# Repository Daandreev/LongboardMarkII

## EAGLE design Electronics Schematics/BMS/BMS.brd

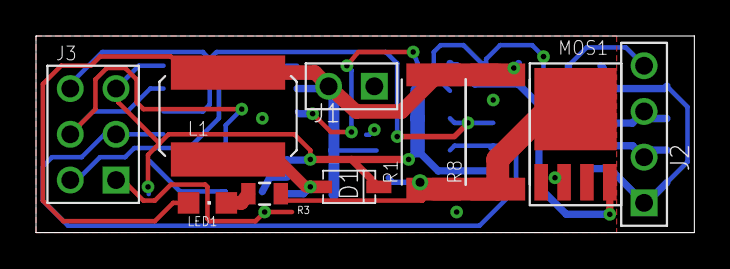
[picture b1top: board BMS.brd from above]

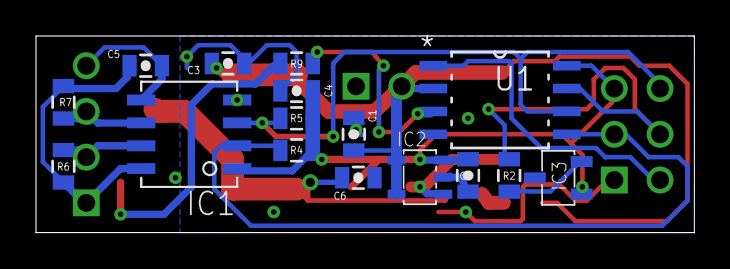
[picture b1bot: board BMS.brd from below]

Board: 2 copper layers, 36.6 x 10.9 mm, 26 parts (16 on the bottom side), 17 nets.

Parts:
C1, C2, C3, C4, C5, C6: 10uF; 0805-CAP
D1: DIODE_SCHOTTKYSOD-123; SOD-123
IC1: SI8600_DUALCHANNELISO; SOIC-8
IC2: SP6641; SOT-23
IC3: TEMP_MCP9701; SOT-23-3
J1: CONNECTOR_2PIN; 2PIN_.1'
J2: CONNECTOR_4PIN; 4PIN_.1'
J3: ISPHEADER; 2X3PIN_.1'
L1: 22uH; 6X6MM_IND
LED1: CHIPLED_0805
MOS1: MOS_N_LOGIC_PSMN7R0; LFPAK
R1, R8: 3.3; 2512_(6432_METRIC)
R2, R3: 390; 0805
R4, R5, R6, R7: 10k; 0805
R9: 180; 0805
U1: ATTINY85-20SU; SOIC127P798X216-8N

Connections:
5V: C2.1, C4.1, D1.CATHODE, IC1.P$1, IC2.3, IC3.1, J3.P$2, R4.2, R5.2, U1.8
5V_VIR: C5.1, IC1.P$8, J2.P$1, R6.2, R7.2
GATE: R9.1, U1.3
GND: C1.1, C2.2, C3.2, C4.2, C6.2, IC1.P$4, IC2.2, IC3.3, J1.P$1, J3.P$6, MOS1.P$1, MOS1.P$2, MOS1.P$3, U1.4
GND_VIR: C5.2, IC1.P$5, J2.P$4
MISO: IC1.P$3, J3.P$1, R5.1, U1.6
MOSI: IC1.P$2, J3.P$4, R4.1, U1.5
unnamed: MOS1.P$4, R9.2
unnamed: LED1.C, R3.2
unnamed: C6.1, MOS1.P$5, R1.P$1, R3.1, R8.P$1
unnamed: IC3.2, R2.2
unnamed: D1.ANODE, IC2.1, L1.P$1
RESET: J3.P$5, U1.1
SCK: J3.P$3, R2.1, U1.7
SCL: IC1.P$6, J2.P$3, R7.1
SDA: IC1.P$7, J2.P$2, R6.1
VBAT: C1.2, C3.1, IC2.4, IC2.5, J1.P$2, L1.P$2, LED1.A, R1.P$2, R8.P$2, U1.2

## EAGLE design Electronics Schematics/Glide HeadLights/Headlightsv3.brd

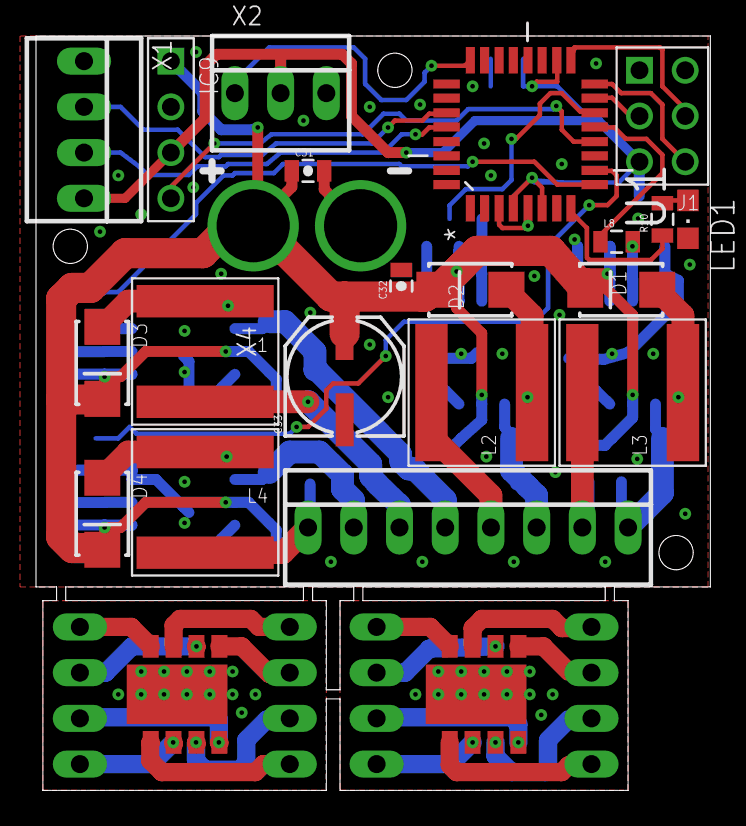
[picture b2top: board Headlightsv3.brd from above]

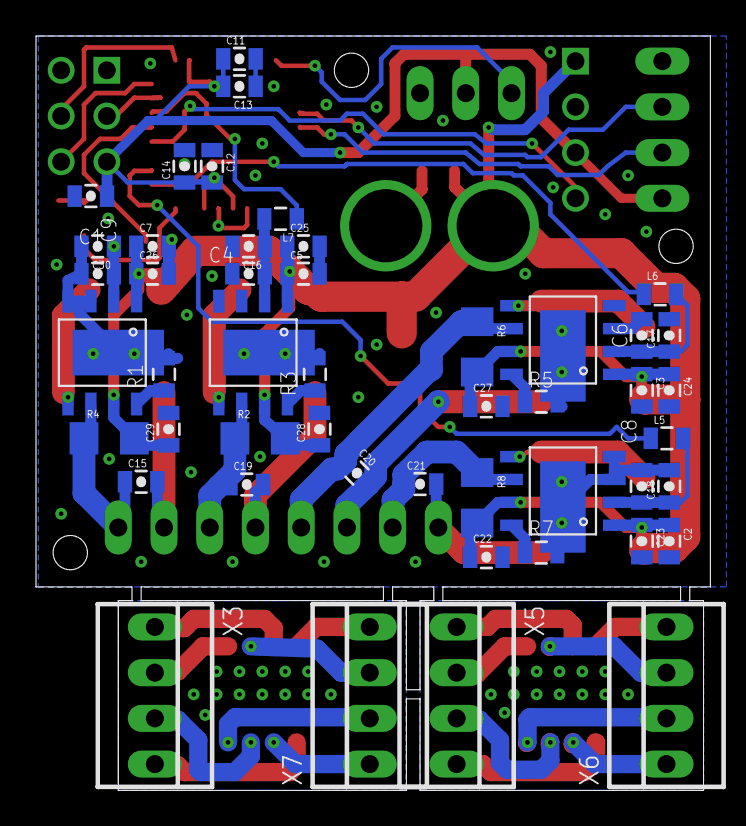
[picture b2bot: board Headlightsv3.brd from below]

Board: 2 copper layers, 37.5 x 41.9 mm, 70 parts (48 on the bottom side), 52 nets.

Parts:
C1, C4, C6, C8: 10uF; 0805-CAP
C2, C3, C5, C7, C9, C13, C14, C15, C19, C20, C21, C22, C27, C28, C29, C32: 1uF; 0805-CAP
C11, C12, C16, C17, C18, C23, C24, C25, C26, C30, C31: 0.1uF; 0805-CAP
C33: NIPPON_F80
D1, D2, D3, D4: SMA-DIODE_ALT
IC1, IC3, IC4, IC5: ILD6150_LED_DRIVER; PG-DSO-8-27
IC2, IC6: LED_RGBW_CONF2; LED_RGBW_CUSTOM
IC9: 5VBUCK_DANNY_CUSTOM_PCB; 4PIN_.1'
J1: ISPHEADER; 2X3PIN_.1'
L1, L2, L3, L4: 33uH; 8X8MM_IND
L5, L6, L7, L8: 0805
LED1: CHIPLED_0805
R1, R3, R5, R7: 10k; 0805
R2, R4, R6, R8: .22; 1206
R10: 1k; 0805
U1: ATMEGA328P-AU; QFP80P900X900X120-32N
X1, X3, X5, X6, X7: 22-23-2041
X2: 22-23-2031
X4: 22-23-2081

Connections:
5V: C9.1, C11.1, C12.2, C13.2, C14.1, IC9.P$3, J1.P$2, U1.4, U1.6, U1.18, X1.4, X2.2
BA: C20.2, L1.P$1, X4.3
BA1: IC6.6, X7.3
BAO: IC2.6, X6.3
BC: C20.1, IC4.P$6, R6.1, X4.4
BC1: IC6.5, X3.2
BCO: IC2.5, X5.2
DIMB: L6.1, U1.9
DIMG: L7.1, U1.14
DIMR: L8.1, U1.13
DIMW: L5.1, U1.10
GA: C19.2, L2.P$1, X4.5
GA1: IC6.4, X7.2
GAO: IC2.4, X6.2
GC: C19.1, IC3.P$6, R2.1, X4.6
GC1: IC6.3, X3.3
GCO: IC2.3, X5.3
GND: C1.2, C2.2, C3.2, C4.2, C5.2, C6.2, C7.2, C8.2, C9.2, C11.2, C12.1, C13.1, C14.2, C16.2, C17.2, C18.2, C22.2, C23.2, C24.2, C25.2, C26.2, C27.2, C28.2, C29.2, C30.2, C31.2, C32.2, C33.-, IC1.P$3, IC1.P$4, IC1.P$9, IC3.P$3, IC3.P$4, IC3.P$9, IC4.P$3, IC4.P$4, IC4.P$9, IC5.P$3, IC5.P$4, IC5.P$9, IC9.P$2, J1.P$6, LED1.C, R1.2, R3.2, R5.2, R7.2, U1.3, U1.5, X1.1, X2.3
LEDG: R10.1, U1.8
MISO: J1.P$1, U1.16
MOSI: J1.P$4, U1.15
unnamed: IC1.P$8, R1.1
unnamed: IC3.P$8, R3.1
unnamed: D2.A, IC3.P$5, L2.P$2
unnamed: IC4.P$8, R5.1
unnamed: D1.A, IC1.P$5, L3.P$2
unnamed: D3.A, IC4.P$5, L1.P$2
unnamed: IC5.P$8, R7.1
unnamed: D4.A, IC5.P$5, L4.P$2
unnamed: LED1.A, R10.2
PWMB: C6.1, C17.1, IC4.P$2, L6.2
PWMG: C4.1, C16.1, IC3.P$2, L7.2
PWMR: C1.1, C30.1, IC1.P$2, L8.2
PWMW: C8.1, C18.1, IC5.P$2, L5.2
RA: C15.2, L3.P$1, X4.7
RA1: IC6.2, X7.1
RAO: IC2.2, X6.1
RC: C15.1, IC1.P$6, R4.1, X4.8
RC1: IC6.1, X3.4
RCO: IC2.1, X5.4
SCK: J1.P$3, U1.17
SCL: U1.28, X1.3
SDA: U1.27, X1.2
SHDN: IC9.P$4, U1.12
TEMP1: U1.24, X2.1
VBAT: C2.1, C3.1, C5.1, C7.1, C22.1, C23.1, C24.1, C25.1, C26.1, C27.1, C28.1, C29.1, C31.1, C32.1, C33.+, D1.C, D2.C, D3.C, D4.C, IC1.P$1, IC1.P$7, IC3.P$1, IC3.P$7, IC4.P$1, IC4.P$7, IC5.P$1, IC5.P$7, IC9.P$1, R2.2, R4.2, R6.2, R8.2
WA: C21.2, L4.P$1, X4.1
WA1: IC6.8, X7.4
WAO: IC2.8, X6.4
WC: C21.1, IC5.P$6, R8.1, X4.2
WC1: IC6.7, X3.1
WCO: IC2.7, X5.1

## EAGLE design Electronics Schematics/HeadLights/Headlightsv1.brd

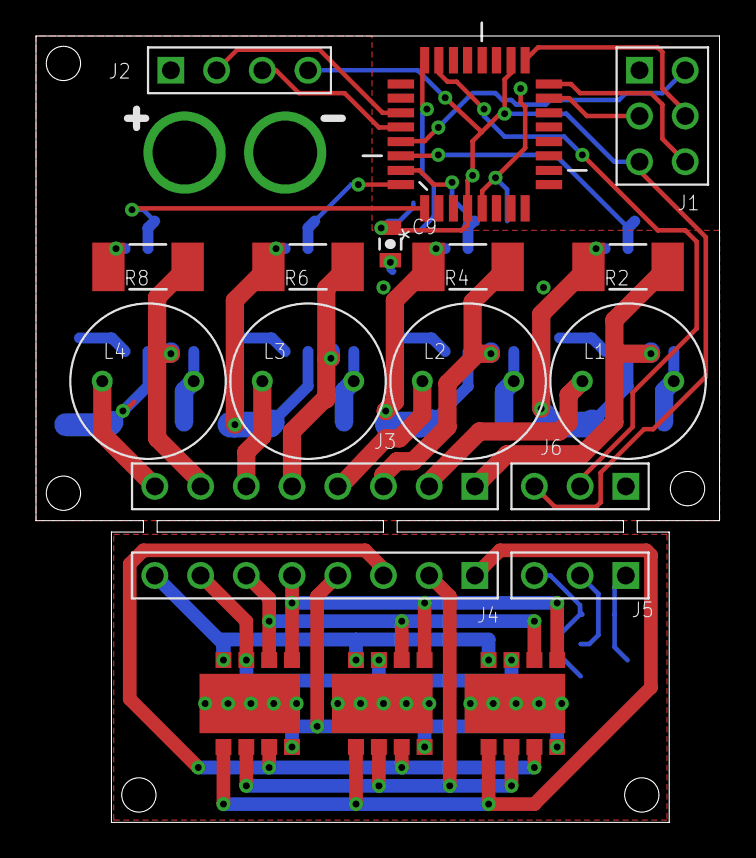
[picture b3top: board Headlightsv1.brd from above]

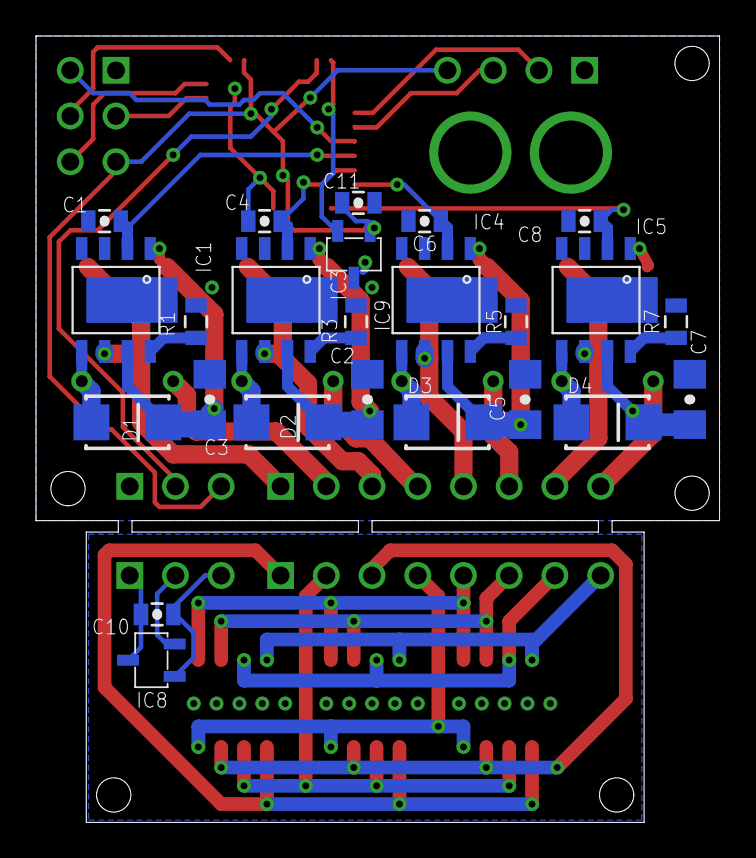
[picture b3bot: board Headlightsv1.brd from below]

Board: 2 copper layers, 38.0 x 43.7 mm, 43 parts (24 on the bottom side), 43 nets.

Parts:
C1, C4, C6, C8: 10uF; 0805-CAP
C2, C3, C5, C7: 1uF; 1206-CAP
C9, C10, C11: 0.33uF; 0805-CAP
D1, D2, D3, D4: SMA-DIODE_ALT
IC1, IC3, IC4, IC5: ILD6150_LED_DRIVER; PG-DSO-8-27
IC2, IC6, IC7: LED_RGBW_CONF2; LED_RGBW_CUSTOM
IC8, IC9: TEMP_MCP9701; SOT-23-3
J1: ISPHEADER; 2X3PIN_.1'
J2: CONNECTOR_4PIN; 4PIN_.1'
J3, J4: CONNECTOR_8PIN; 8PIN_.1'
J5, J6: CONNECTOR_3PIN; 3PIN_.1'
L1, L2, L3, L4: 33uH; IND_RLB_SERIES
R1, R3, R5, R7: 10k; 0805
R2, R4, R6, R8: .11; R2010
U1: ATTINY48-AU; QFP80P900X900X120-32N

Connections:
5V: C9.1, C11.1, IC9.1, J1.P$2, J2.P$4, J6.P$3, U1.4, U1.18
5VO: C10.2, IC8.1, J5.P$3
BA: J3.P$6, L3.P$1
BAO: IC2.6, IC6.6, IC7.6, J4.P$6
BC: IC4.P$6, J3.P$5, R6.1
BCO: IC2.5, IC6.5, IC7.5, J4.P$5
DIMB: C6.1, IC4.P$2, U1.32
DIMG: C4.1, IC3.P$2, U1.31
DIMR: C1.1, IC1.P$2, U1.30
DIMW: C8.1, IC5.P$2, U1.1
GA: J3.P$4, L2.P$1
GAO: IC2.4, IC6.4, IC7.4, J4.P$4
GC: IC3.P$6, J3.P$3, R4.1
GCO: IC2.3, IC6.3, IC7.3, J4.P$3
GND: C1.2, C2.2, C3.2, C4.2, C5.2, C6.2, C7.2, C8.2, C9.2, C11.2, IC1.P$3, IC1.P$4, IC1.P$9, IC3.P$3, IC3.P$4, IC3.P$9, IC4.P$3, IC4.P$4, IC4.P$9, IC5.P$3, IC5.P$4, IC5.P$9, IC9.3, J1.P$6, J2.P$1, J6.P$1, R1.2, R3.2, R5.2, R7.2, U1.5
GNDO: C10.1, IC8.3, J5.P$1
HEAT: IC2.9, IC6.9, IC7.9
MISO: J1.P$1, U1.16
MOSI: J1.P$4, U1.15
unnamed: IC1.P$8, R1.1
unnamed: IC3.P$8, R3.1
unnamed: D2.A, IC3.P$5, L2.P$2
unnamed: IC4.P$8, R5.1
unnamed: D1.A, IC1.P$5, L1.P$2
unnamed: D3.A, IC4.P$5, L3.P$2
unnamed: IC5.P$8, R7.1
unnamed: D4.A, IC5.P$5, L4.P$2
RA: J3.P$2, L1.P$1
RAO: IC2.2, IC6.2, IC7.2, J4.P$2
RC: IC1.P$6, J3.P$1, R2.1
RCO: IC2.1, IC6.1, IC7.1, J4.P$1
RESET: J1.P$5, U1.29
SCK: J1.P$3, U1.17
SCL: J2.P$3, U1.28
SDA: J2.P$2, U1.27
TEMP1: J6.P$2, U1.23
TEMP1O: IC8.2, J5.P$2
TEMP2: IC9.2, U1.24
VBAT: C2.1, C3.1, C5.1, C7.1, D1.C, D2.C, D3.C, D4.C, IC1.P$1, IC1.P$7, IC3.P$1, IC3.P$7, IC4.P$1, IC4.P$7, IC5.P$1, IC5.P$7, R2.2, R4.2, R6.2, R8.2
WA: J3.P$8, L4.P$1
WAO: IC2.8, IC6.8, IC7.8, J4.P$8
WC: IC5.P$6, J3.P$7, R8.1
WCO: IC2.7, IC6.7, IC7.7, J4.P$7

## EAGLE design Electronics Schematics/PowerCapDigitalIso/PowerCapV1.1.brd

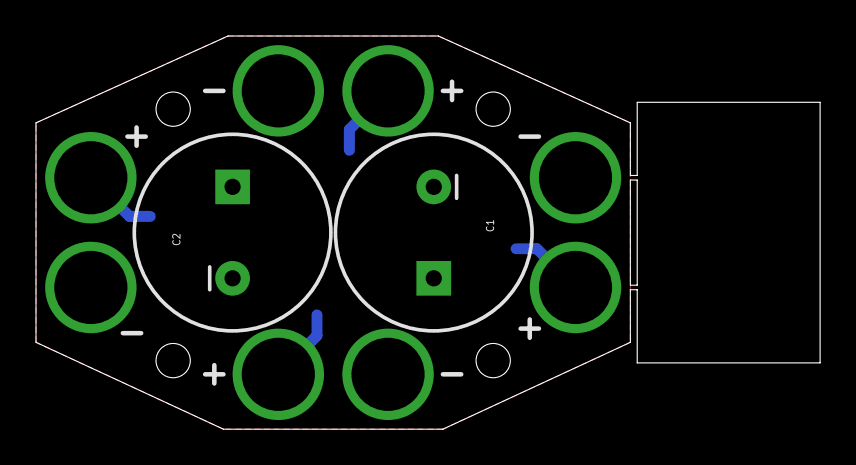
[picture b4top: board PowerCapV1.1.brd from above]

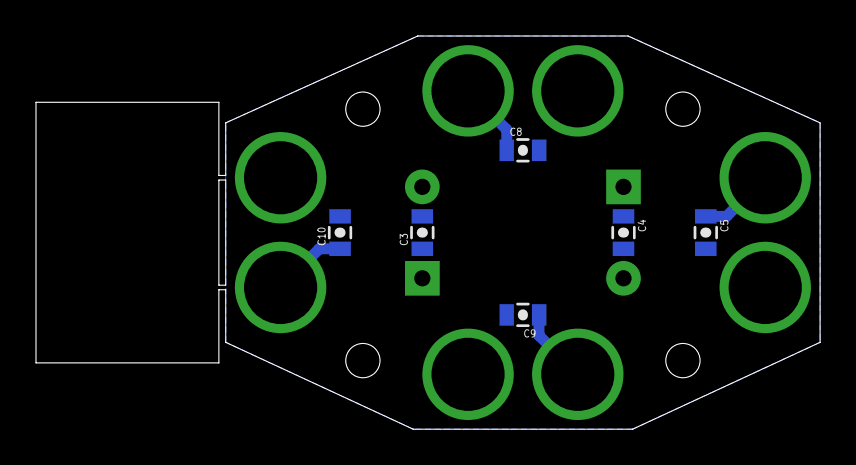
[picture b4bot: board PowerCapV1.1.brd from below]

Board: 2 copper layers, 43.6 x 21.8 mm, 8 parts (6 on the bottom side), 2 nets.

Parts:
C1, C2: CPOL-RADIAL-1000UF-25V
C3, C4, C5, C8, C9, C10: 1uF; 0805-CAP

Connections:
VABT: C1.-, C2.-, C3.2, C4.2, C5.2, C8.2, C9.2, C10.2
VBAT: C1.+, C2.+, C3.1, C4.1, C5.1, C8.1, C9.1, C10.1

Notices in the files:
parts and their libraries:
SparkFun-Capacitors: Licensing: Creative Commons ShareAlike 4.0 International - https://creativecommons.org/licenses/by-sa/4.0
